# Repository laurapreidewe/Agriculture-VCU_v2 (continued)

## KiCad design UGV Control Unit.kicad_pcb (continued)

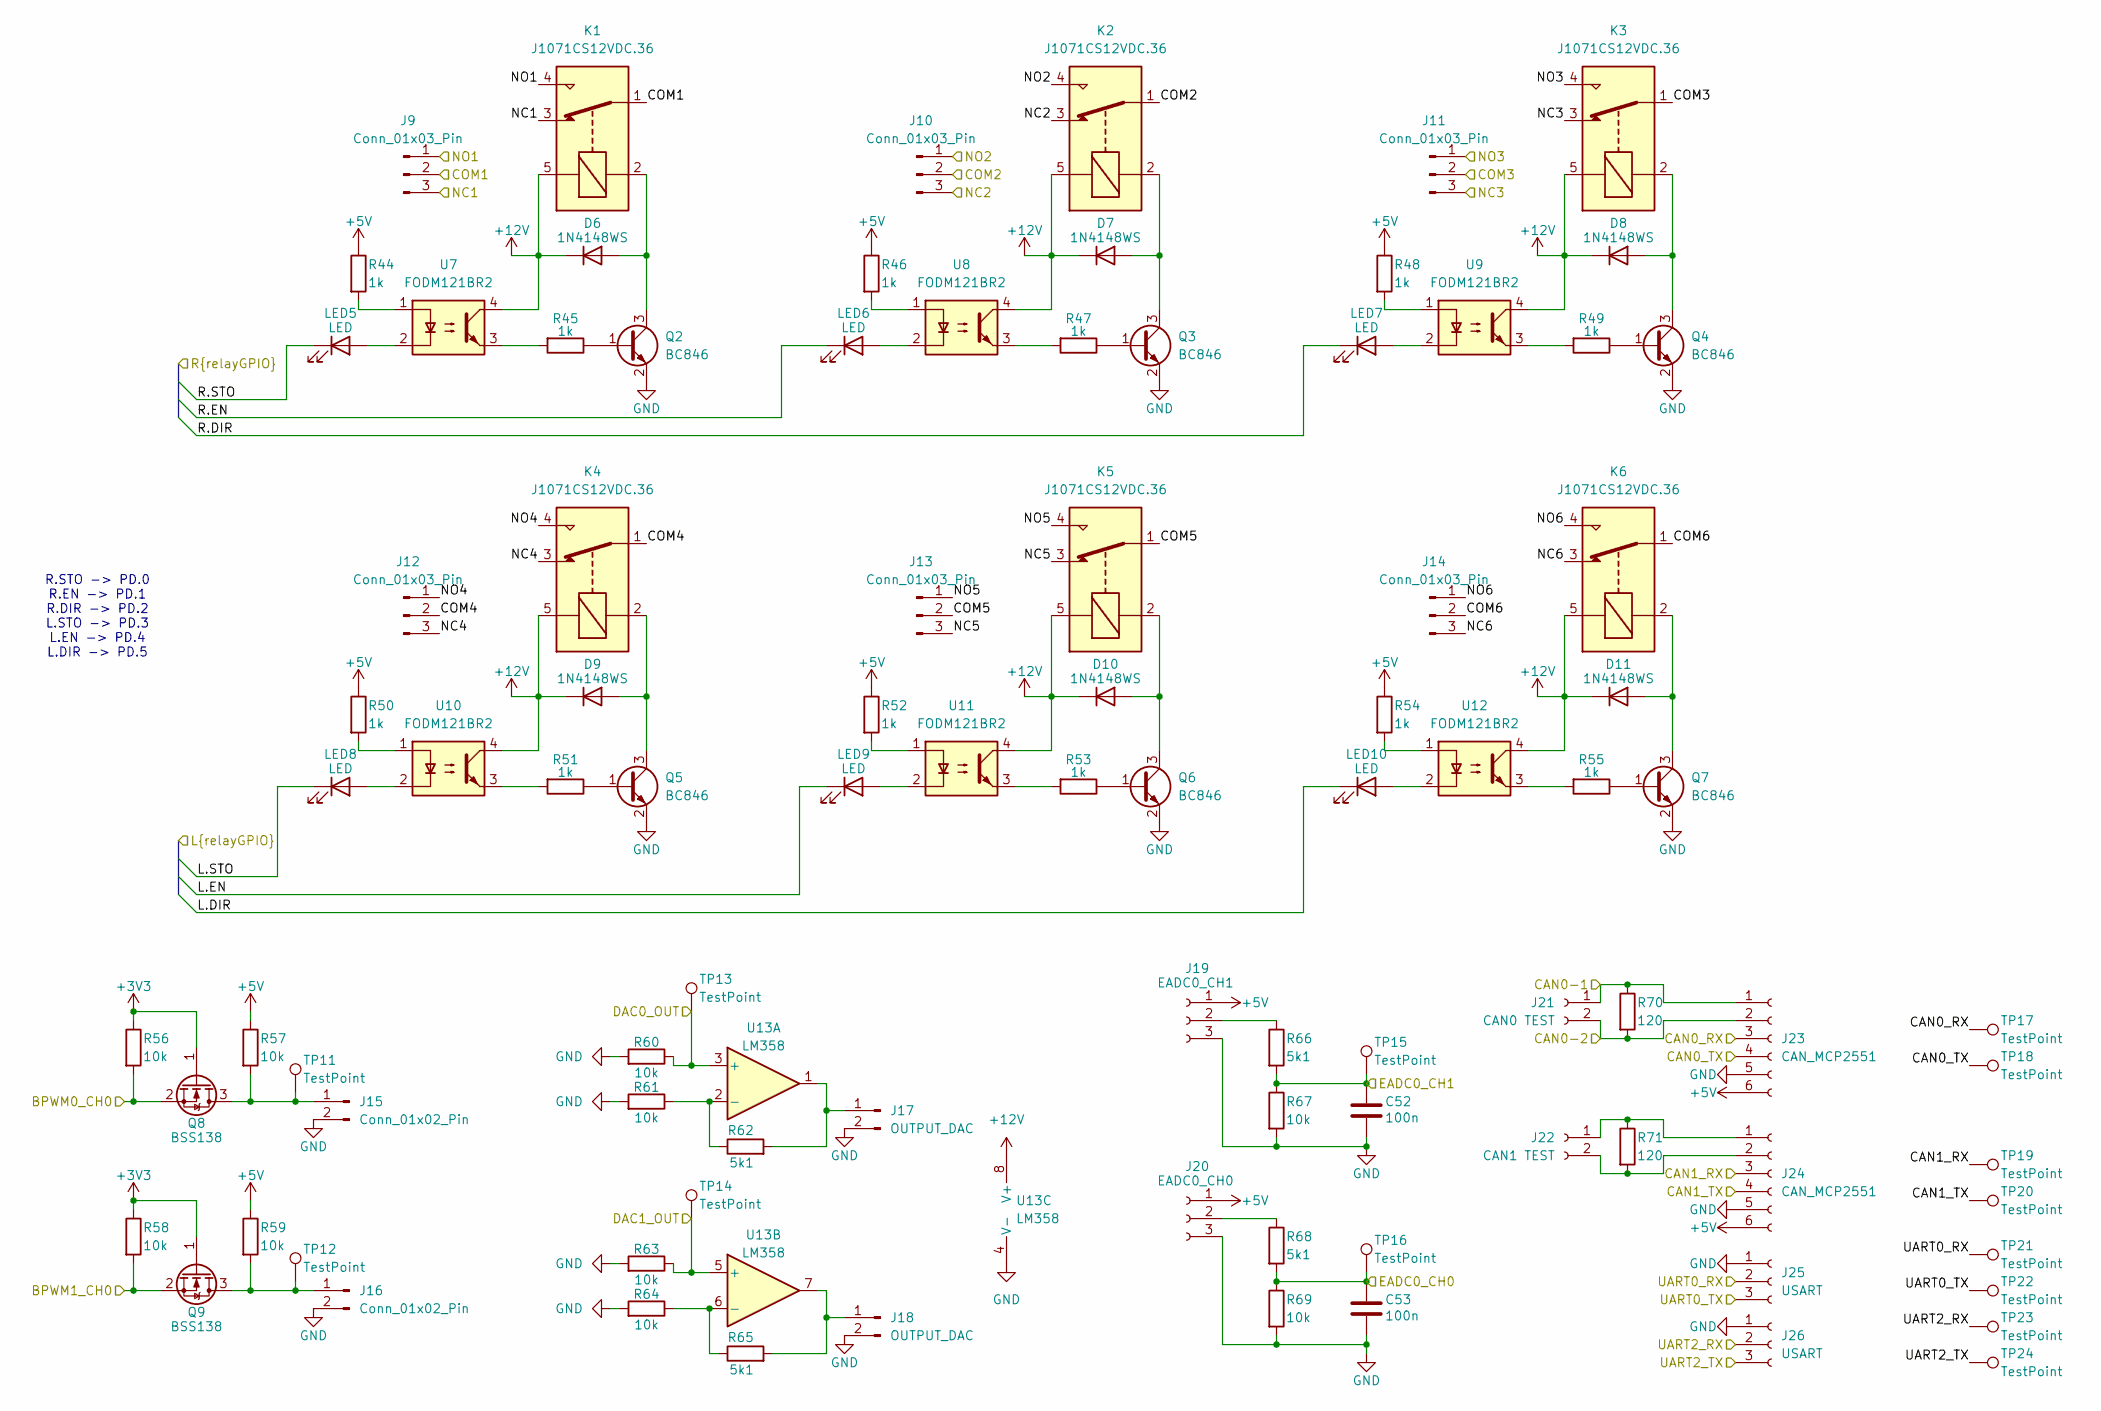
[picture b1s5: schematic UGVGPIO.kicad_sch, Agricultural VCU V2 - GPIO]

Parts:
C52, C53: 100n; C_0603_1608Metric_Pad1.08x0.95mm_HandSolder; MANUFACTURER_PART_NUMBER KGM15BR71H104KT
D6, D7, D8, D9, D10, D11: 1N4148WS; D_SOD-323; MANUFACTURER_PART_NUMBER 1N4148WS
J9, J10, J11, J12, J13, J14: Conn_01x03_Pin; Wuerth_TBL_691137710003_1x03_P5mm; MANUFACTURER_PART_NUMBER 691137710003
J15, J16: Conn_01x02_Pin; Molex_SL_171971-0002_1x02_P2.54mm_Vertical; MANUFACTURER_PART_NUMBER 1719710002
J17, J18: OUTPUT_DAC; Molex_SL_171971-0002_1x02_P2.54mm_Vertical; MANUFACTURER_PART_NUMBER 1719710002
J19: EADC0_CH1; Molex_SL_171971-0003_1x03_P2.54mm_Vertical; MANUFACTURER_PART_NUMBER 1719710003
J20: EADC0_CH0; Molex_SL_171971-0003_1x03_P2.54mm_Vertical; MANUFACTURER_PART_NUMBER 1719710003
J21: CAN0 TEST; Wuerth_TBL_691137710002_1x02_P5mm; MANUFACTURER_PART_NUMBER 691137710002
J22: CAN1 TEST; Wuerth_TBL_691137710002_1x02_P5mm; MANUFACTURER_PART_NUMBER 691137710002
J23, J24: CAN_MCP2551; PinSocket_1x06_P2.54mm_Vertical; MANUFACTURER_PART_NUMBER 61300611821
J25, J26: USART; Molex_SL_171971-0003_1x03_P2.54mm_Vertical; MANUFACTURER_PART_NUMBER 1719710003
K1, K2, K3, K4, K5, K6: J1071CS12VDC.36; Relay_SPDT_J1071CSXXVDC.36; MANUFACTURER_PART_NUMBER J1071CS12VDC.36
LED5, LED6, LED7, LED8, LED9, LED10: LED; LED_0603_1608Metric_Pad1.05x0.95mm_HandSolder; MANUFACTURER_PART_NUMBER 150060SS75003
Q2, Q3, Q4, Q5, Q6, Q7: BC846; SOT-23; MANUFACTURER_PART_NUMBER BC846,215
Q8, Q9: BSS138; SOT-23; MANUFACTURER_PART_NUMBER BSS138
R44, R45, R46, R47, R48, R49, R50, R51, R52, R53, R54, R55: 1k; R_0603_1608Metric_Pad0.98x0.95mm_HandSolder; MANUFACTURER_PART_NUMBER RT0603FRE131KL
R56, R57, R58, R59, R60, R61, R63, R64, R67, R69: 10k; R_0603_1608Metric_Pad0.98x0.95mm_HandSolder; MANUFACTURER_PART_NUMBER RT0603FRE0710KL
R62, R65, R66, R68: 5k1; R_0603_1608Metric_Pad0.98x0.95mm_HandSolder; MANUFACTURER_PART_NUMBER RT0603BRD075K1L
R70, R71: 120; R_0603_1608Metric_Pad0.98x0.95mm_HandSolder; MANUFACTURER_PART_NUMBER RT0603FRE13120RL
TP11, TP12, TP13, TP14, TP15, TP16, TP17, TP18, TP19, TP20, TP21, TP22, TP23, TP24: TestPoint; PinHeader_1x01_P2.54mm_Vertical
U7, U8, U9, U10, U11, U12: FODM121BR2; MFSOP6-4_4.4x3.6mm_P1.27mm; MANUFACTURER_PART_NUMBER FODM121BR2
U13: LM358; SOIC-8_3.9x4.9mm_P1.27mm; MANUFACTURER_PART_NUMBER LM358M/NOPB

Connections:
+12V: D6.1 (K), D7.1 (K), D8.1 (K), D9.1 (K), D10.1 (K), D11.1 (K), K1.5, K2.5, K3.5, K4.5, K5.5, K6.5, U7.4, U8.4, U9.4, U10.4, U11.4, U12.4, U13.8 (V+); also elsewhere on the board
/UGV - GPIO/CAN0_RX: J23.3, TP17.1; also elsewhere on the board
/UGV - GPIO/CAN0_TX: J23.4, TP18.1; also elsewhere on the board
/UGV - GPIO/CAN1_RX: J24.3, TP19.1; also elsewhere on the board
/UGV - GPIO/CAN1_TX: J24.4, TP20.1; also elsewhere on the board
/UGV - GPIO/COM1: J9.2, K1.1
/UGV - GPIO/COM2: J10.2, K2.1
/UGV - GPIO/COM3: J11.2, K3.1
/UGV - GPIO/COM4: J12.2, K4.1
/UGV - GPIO/COM5: J13.2, K5.1
/UGV - GPIO/COM6: J14.2, K6.1
/UGV - GPIO/L.DIR: LED10.1 (K); also elsewhere on the board
/UGV - GPIO/L.EN: LED9.1 (K); also elsewhere on the board
/UGV - GPIO/L.STO: LED8.1 (K); also elsewhere on the board
/UGV - GPIO/NC1: J9.3, K1.3
/UGV - GPIO/NC2: J10.3, K2.3
/UGV - GPIO/NC3: J11.3, K3.3
/UGV - GPIO/NC4: J12.3, K4.3
/UGV - GPIO/NC5: J13.3, K5.3
/UGV - GPIO/NC6: J14.3, K6.3
/UGV - GPIO/NO1: J9.1, K1.4
/UGV - GPIO/NO2: J10.1, K2.4
/UGV - GPIO/NO3: J11.1, K3.4
/UGV - GPIO/NO4: J12.1, K4.4
/UGV - GPIO/NO5: J13.1, K5.4
/UGV - GPIO/NO6: J14.1, K6.4
/UGV - GPIO/UART0_RX: J25.2, TP21.1; also elsewhere on the board
/UGV - GPIO/UART0_TX: J25.3, TP22.1; also elsewhere on the board
/UGV - GPIO/UART2_RX: J26.2, TP23.1; also elsewhere on the board
/UGV - GPIO/UART2_TX: J26.3, TP24.1; also elsewhere on the board
/UGV - MCU/PB.0: C53.1, R68.2, R69.1, TP16.1; also elsewhere on the board
/UGV - MCU/PB.1: C52.1, R66.2, R67.1, TP15.1; also elsewhere on the board
/UGV - MCU/PB.11: Q9.2 (S), R58.2; also elsewhere on the board
/UGV - MCU/PB.12: R60.1, TP13.1, U13.3 (+); also elsewhere on the board
/UGV - MCU/PB.13: R63.1, TP14.1, U13.5 (+); also elsewhere on the board
/UGV - MCU/PD.0: LED5.1 (K); also elsewhere on the board
/UGV - MCU/PD.1: LED6.1 (K); also elsewhere on the board
/UGV - MCU/PD.2: LED7.1 (K); also elsewhere on the board
/UGV - MCU/PJ.13: Q8.2 (S), R56.2; also elsewhere on the board
GND: C52.2, C53.2, J15.2, J16.2, J17.2, J18.2, J19.3, J20.3, J23.5, J24.5, J25.1, J26.1, Q2.2 (E), Q3.2 (E), Q4.2 (E), Q5.2 (E), Q6.2 (E), Q7.2 (E), R60.2, R61.2, R63.2, R64.2, R67.2, R69.2, U13.4 (V-); also elsewhere on the board
unnamed: D6.2 (A), K1.2, Q2.3 (C)
unnamed: D7.2 (A), K2.2, Q3.3 (C)
unnamed: D8.2 (A), K3.2, Q4.3 (C)
unnamed: D9.2 (A), K4.2, Q5.3 (C)
unnamed: D10.2 (A), K5.2, Q6.3 (C)
unnamed: D11.2 (A), K6.2, Q7.3 (C)
unnamed: J15.1, Q8.3 (D), R57.2, TP11.1
unnamed: J16.1, Q9.3 (D), R59.2, TP12.1
unnamed: J17.1, R62.2, U13.1
unnamed: J18.1, R65.2, U13.7
unnamed: J19.2, R66.1
unnamed: J20.2, R68.1
unnamed: J21.1, J23.1, R70.1
unnamed: J21.2, J23.2, R70.2
unnamed: J22.1, J24.1, R71.1
unnamed: J22.2, J24.2, R71.2
unnamed: LED5.2 (A), U7.2
unnamed: LED6.2 (A), U8.2
unnamed: LED7.2 (A), U9.2
unnamed: LED8.2 (A), U10.2
unnamed: LED9.2 (A), U11.2
unnamed: LED10.2 (A), U12.2
unnamed: Q2.1 (B), R45.1
unnamed: Q3.1 (B), R47.1
unnamed: Q4.1 (B), R49.1
unnamed: Q5.1 (B), R51.1
unnamed: Q6.1 (B), R53.1
unnamed: Q7.1 (B), R55.1
unnamed: R44.2, U7.1
unnamed: R45.2, U7.3
unnamed: R46.2, U8.1
unnamed: R47.2, U8.3
unnamed: R48.2, U9.1
unnamed: R49.2, U9.3
unnamed: R50.2, U10.1
unnamed: R51.2, U10.3
unnamed: R52.2, U11.1
unnamed: R53.2, U11.3
unnamed: R54.2, U12.1
unnamed: R55.2, U12.3
unnamed: R61.1, R62.1, U13.2 (-)
unnamed: R64.1, R65.1, U13.6 (-)

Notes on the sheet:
R.STO -> PD.0 R.EN -> PD.1 R.DIR -> PD.2 L.STO -> PD.3 L.EN -> PD.4 L.DIR -> PD.5

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
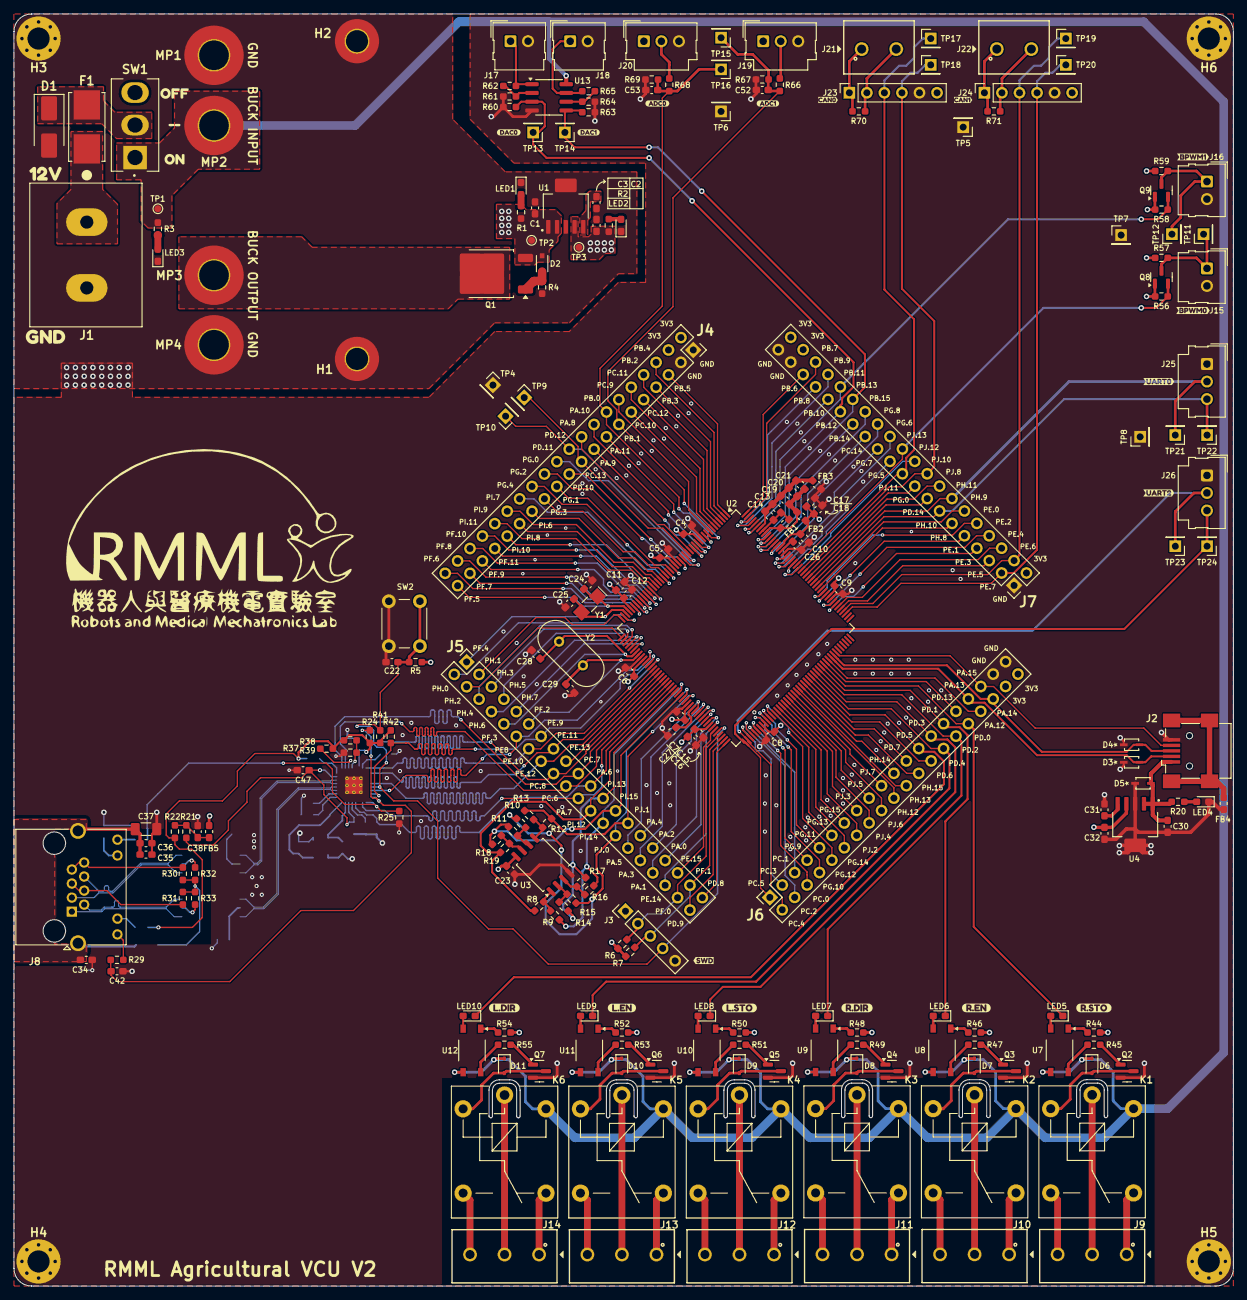
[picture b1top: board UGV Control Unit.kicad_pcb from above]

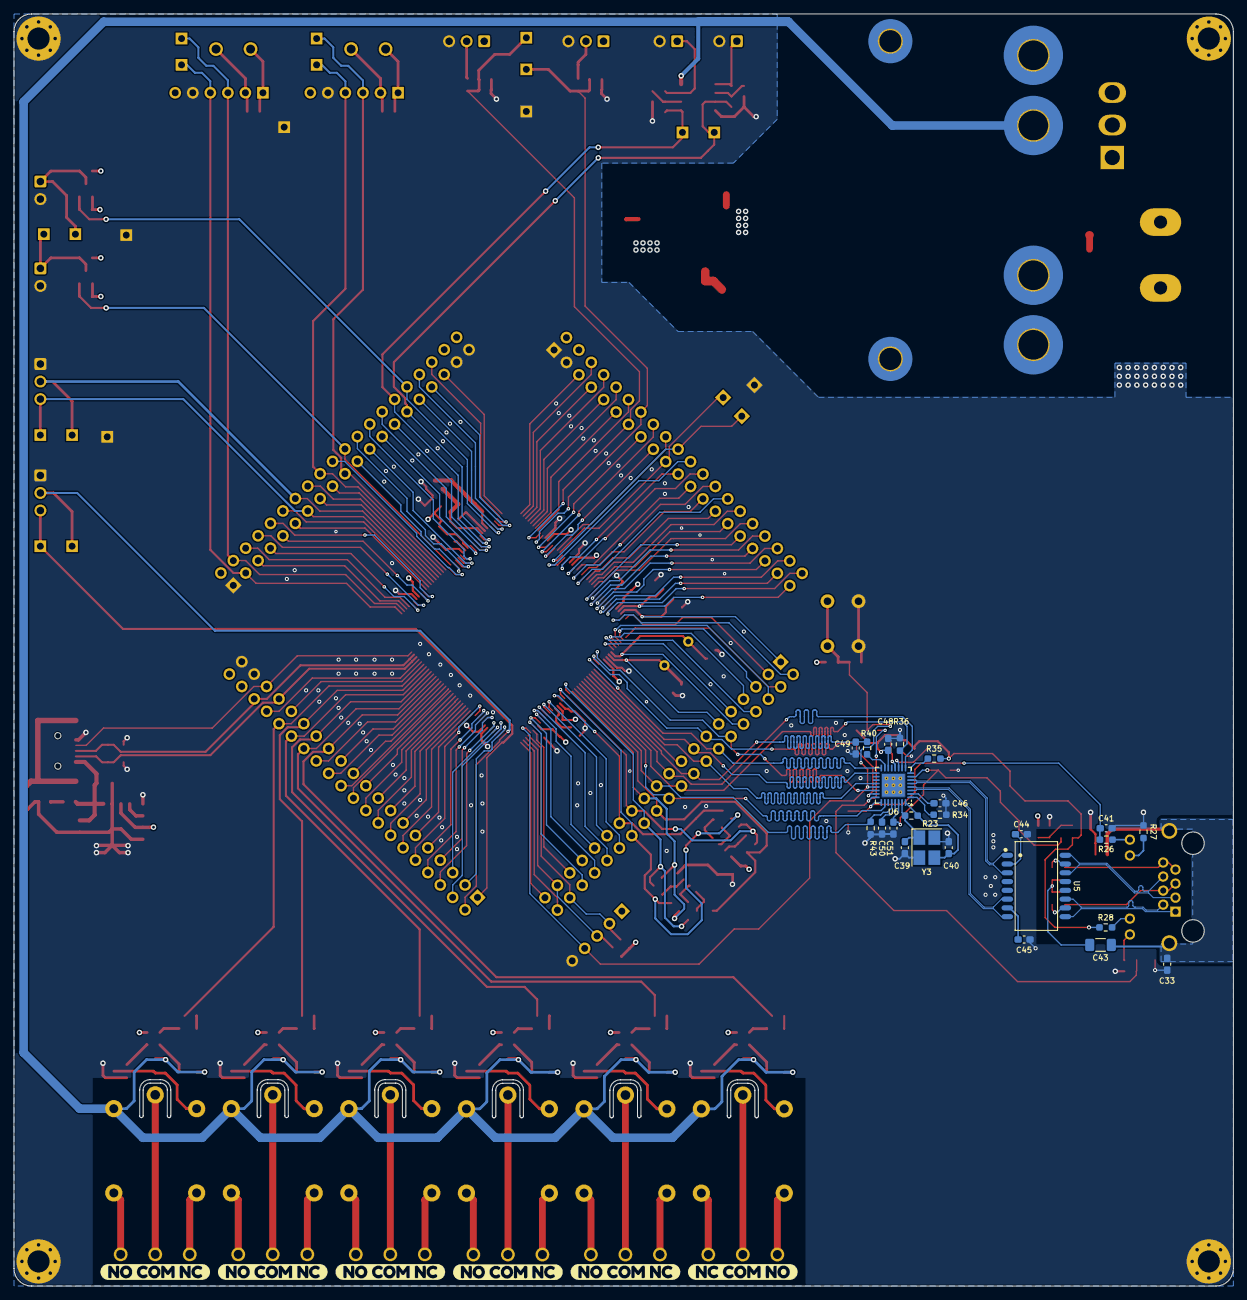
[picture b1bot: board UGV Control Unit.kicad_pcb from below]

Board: 4 copper layers, 176.5 x 184.2 mm, 272 parts (30 on the bottom side), 268 nets.

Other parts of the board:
kibuzzard-69F96702: G***; kibuzzard-69F96702
kibuzzard-69634B4E: G***; kibuzzard-69634B4E
kibuzzard-69634B5D: G***; kibuzzard-69634B5D
kibuzzard-69634B7E: G***; kibuzzard-69634B7E
kibuzzard-69634B14: G***; kibuzzard-69634B14
kibuzzard-69634B71: G***; kibuzzard-69634B71
kibuzzard-69634B86: G***; kibuzzard-69634B86
kibuzzard-69634D58: G***; kibuzzard-69634D58
kibuzzard-69634DF9: G***; kibuzzard-69634DF9
kibuzzard-69634E28: G***; kibuzzard-69634E28
kibuzzard-69634F3E: G***; kibuzzard-69634F3E
kibuzzard-69634F68: G***; kibuzzard-69634F68
kibuzzard-696343CD: G***; kibuzzard-696343CD
kibuzzard-696344FB: G***; kibuzzard-696344FB
kibuzzard-696346AD: G***; kibuzzard-696346AD
kibuzzard-696346DC: G***; kibuzzard-696346DC
kibuzzard-6963491B: G***; kibuzzard-6963491B
kibuzzard-6963492B: G***; kibuzzard-6963492B
kibuzzard-69634563: G***; kibuzzard-69634563
kibuzzard-69634575: G***; kibuzzard-69634575
kibuzzard-69634733: G***; kibuzzard-69634733
kibuzzard-69635000: G***; kibuzzard-69635000
kibuzzard-69635019: G***; kibuzzard-69635019
kibuzzard-69641404, kibuzzard-69641404#2, kibuzzard-69641404#3, kibuzzard-69641404#4, kibuzzard-69641404#5: G***; kibuzzard-69641404
